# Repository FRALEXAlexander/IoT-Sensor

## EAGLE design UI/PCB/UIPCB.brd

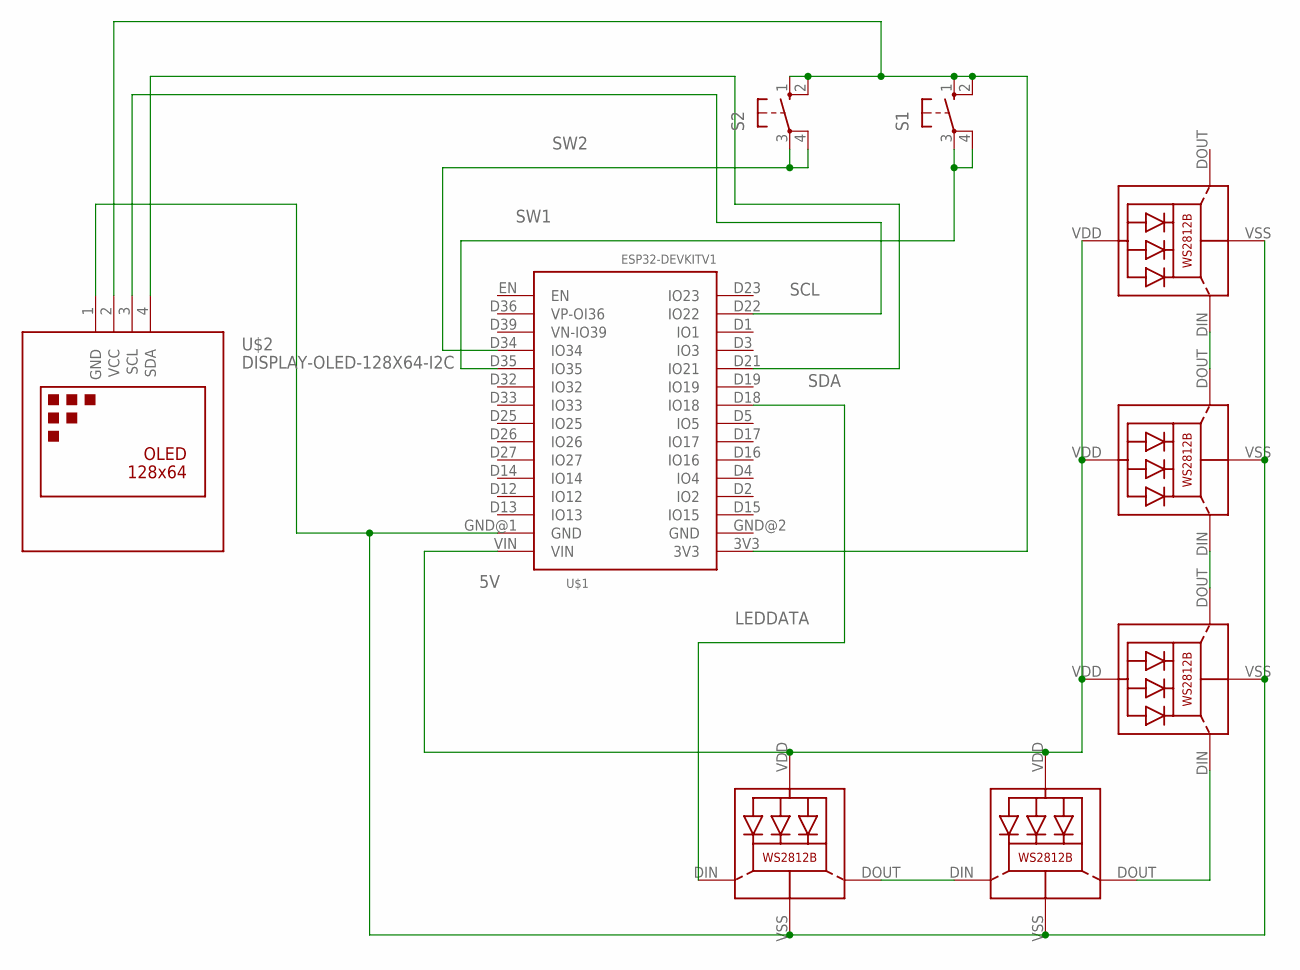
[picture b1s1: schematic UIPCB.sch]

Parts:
LED0, LED1, LED2, LED3, LED4: WS2812B
S1, S2: 10-XX; B3F-10XX
U$1: ESP32DEVKITV1; ESP32-DEVKITV1
U$2: DISPLAY-OLED-128X64-I2C

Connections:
3V3: S1.1 (S), S1.2 (S1), S2.1 (S), S2.2 (S1), U$1.3V3, U$2.2 (VCC)
5V: LED0.VDD, LED1.VDD, LED2.VDD, LED3.VDD, LED4.VDD, U$1.VIN
GND: LED0.VSS (GND), LED1.VSS (GND), LED2.VSS (GND), LED3.VSS (GND), LED4.VSS (GND), U$1.GND@1 (GND), U$2.1 (GND)
LEDDATA: LED0.DIN (DI), U$1.D18 (IO18)
unnamed: LED0.DOUT (DO), LED1.DIN (DI)
unnamed: LED1.DOUT (DO), LED2.DIN (DI)
unnamed: LED2.DOUT (DO), LED3.DIN (DI)
unnamed: LED3.DOUT (DO), LED4.DIN (DI)
SCL: U$1.D22 (IO22), U$2.3 (SCL)
SDA: U$1.D21 (IO21), U$2.4 (SDA)
SW1: S1.3, S1.4 (P1), U$1.D35 (IO35)
SW2: S2.3, S2.4 (P1), U$1.D34 (IO34)

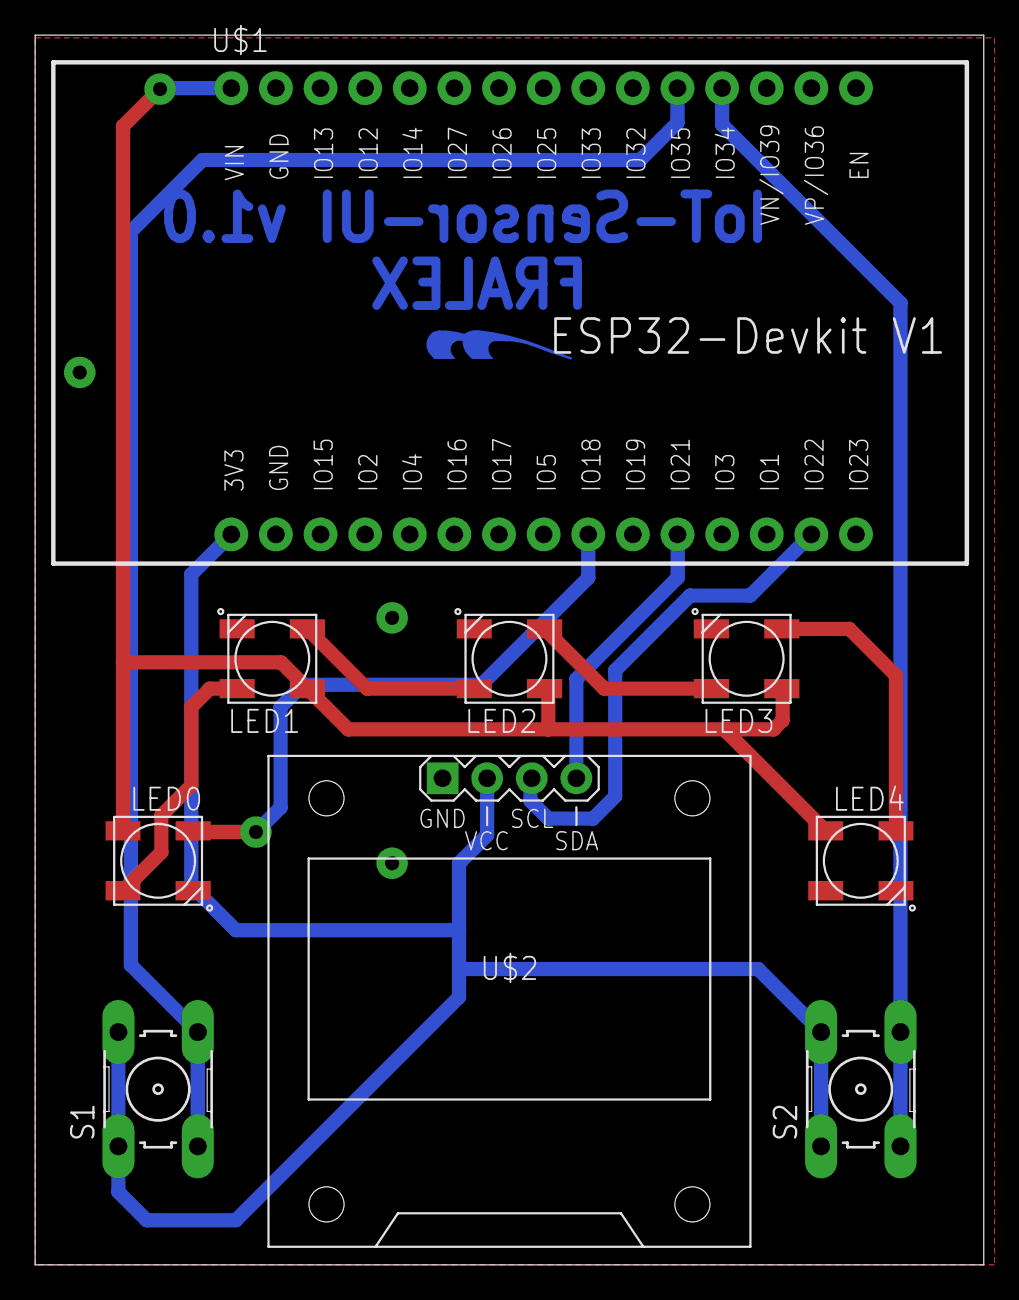
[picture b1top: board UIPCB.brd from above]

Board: 2 copper layers, 54.0 x 70.0 mm, 10 parts (0 on the bottom side), 12 nets.

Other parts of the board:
U$4: LOGOBOTTOM

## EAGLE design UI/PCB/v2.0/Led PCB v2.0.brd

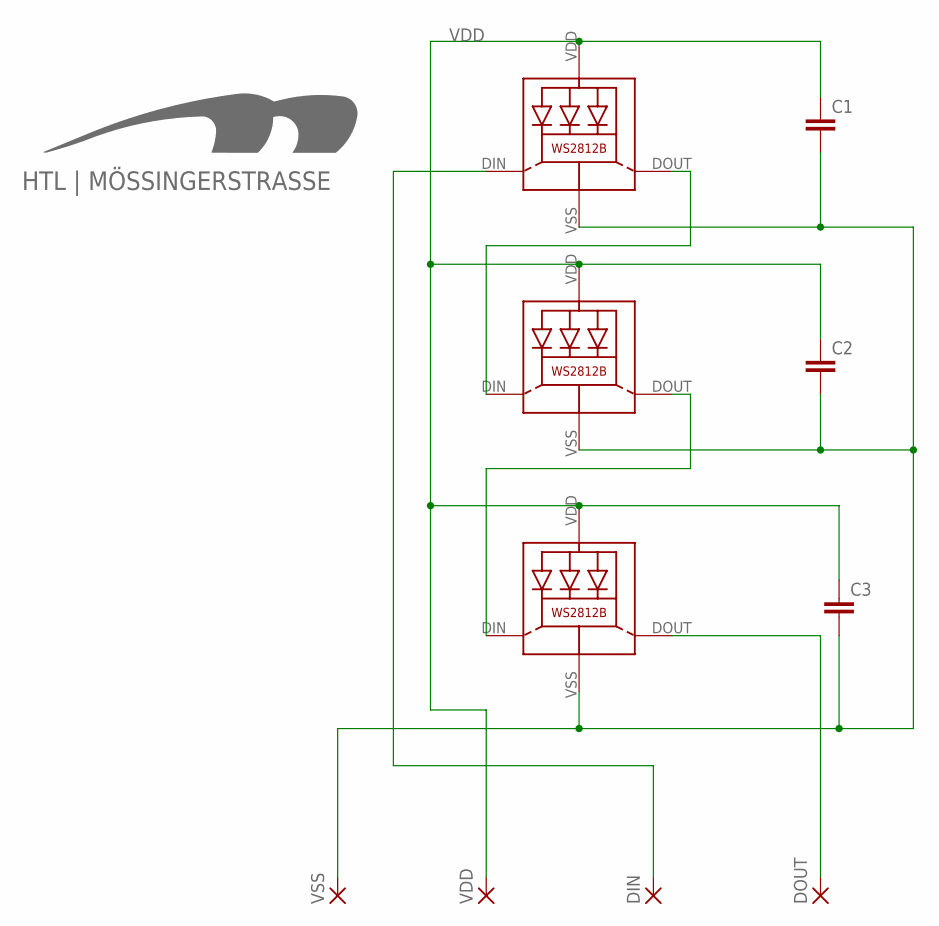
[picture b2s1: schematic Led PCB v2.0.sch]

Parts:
C1, C2, C3: C-EUC0805; C0805
DIN: SMD2; SMD1,27-2,54
DOUT: SMD2; SMD1,27-2,54
LED1, LED2, LED3: WS2812B
U$1: HTL_LOGOTOP_8MM; LOGOTOP_8
VDD: SMD2; SMD1,27-2,54
VSS: SMD2; SMD1,27-2,54

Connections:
DIN: DIN.1, LED1.DIN (DI)
DOUT: DOUT.1, LED3.DOUT (DO)
GND: C1.2, C2.2, C3.2, LED1.VSS (GND), LED2.VSS (GND), LED3.VSS (GND), VSS.1
unnamed: LED2.DOUT (DO), LED3.DIN (DI)
unnamed: LED1.DOUT (DO), LED2.DIN (DI)
VDD: C1.1, C2.1, C3.1, LED1.VDD, LED2.VDD, LED3.VDD, VDD.1

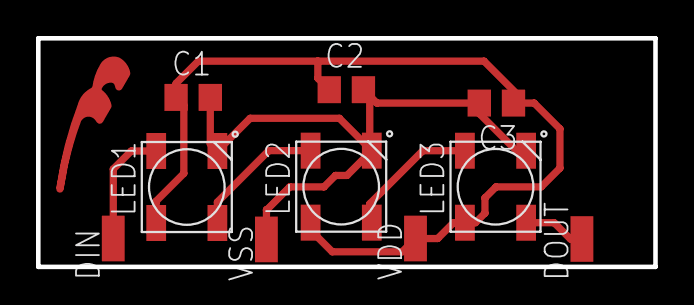
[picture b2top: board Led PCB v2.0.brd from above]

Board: 2 copper layers, 34.3 x 12.7 mm, 11 parts (0 on the bottom side), 6 nets.

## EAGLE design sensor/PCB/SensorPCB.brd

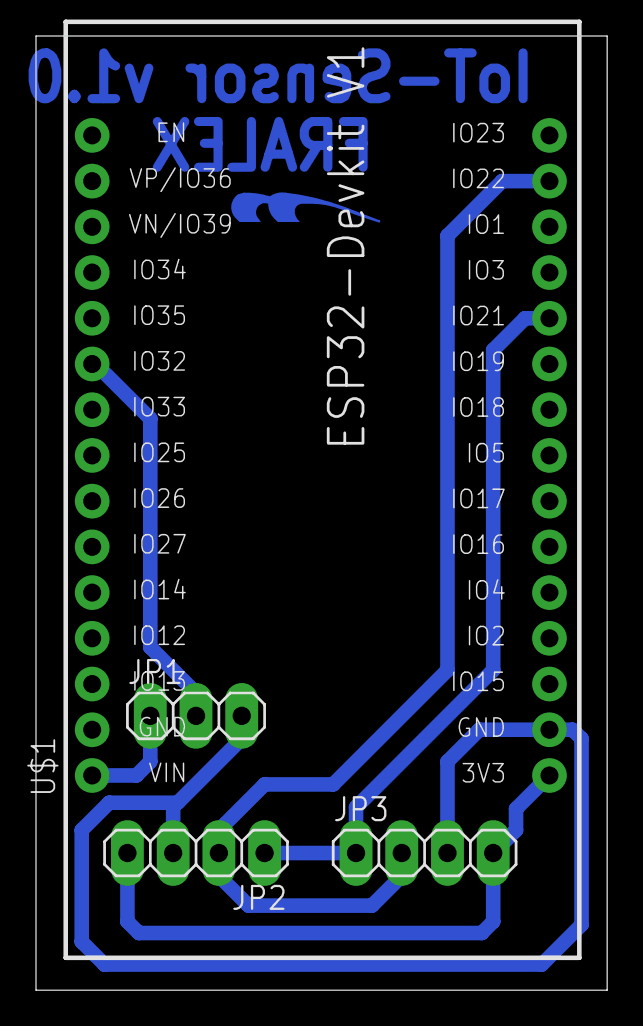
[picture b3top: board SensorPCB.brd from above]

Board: 2 copper layers, 31.7 x 53.0 mm, 5 parts (0 on the bottom side), 6 nets.

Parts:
JP1: 1X03
JP2, JP3: 1X04
U$1: ESP32DEVKITV1; ESP32-DEVKITV1
U$4: LOGOBOTTOM

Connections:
3V3: JP2.4, JP3.4, U$1.3V3
5V: JP1.1, U$1.VIN
GND: JP1.3, JP2.3, JP3.3, U$1.GND@2
MD: JP1.2, U$1.D32
SCL: JP2.2, JP3.2, U$1.D22
SDA: JP2.1, JP3.1, U$1.D21

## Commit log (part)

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2020-02-21 added Sensor PCB and Motionsensor TestScript
2020-02-25 added Script
2020-02-25 moved PCB folder added Case
2020-02-28 added case v2
2020-02-28 added UI Base
2020-02-28 added code for bme / added LED TMP PCB
2020-02-28 Circuit for UI
2020-02-28 Auto stash before merge of "master" and "origin/master"
2020-02-29 added bottom Case changed corner angle
2020-02-29 sorted code added OTA
2020-03-06 added ui board added dashborad basic
2020-03-06 Script Leds
2020-03-13 made it work
2020-04-05 Bump acorn from 6.4.0 to 6.4.1 in /sensor/DASHBOARD
    Bumps [acorn](https://github.com/acornjs/acorn) from 6.4.0 to 6.4.1.
    - [Release notes](https://github.com/acornjs/acorn/releases)
    - [Commits](https://github.com/acornjs/acorn/compare/6.4.0...6.4.1)
2020-06-07 Bump websocket-extensions from 0.1.3 to 0.1.4 in /sensor/DASHBOARD
    Bumps [websocket-extensions](https://github.com/faye/websocket-extensions-node) from 0.1.3 to 0.1.4.
    - [Release notes](https://github.com/faye/websocket-extensions-node/releases)
    - [Changelog](https://github.com/faye/websocket-extensions-node/blob/master/CHANGELOG.md)
    - [Commits](https://github.com/faye/websocket-extensions-node/compare/0.1.3...0.1.4)
2020-07-19 Bump lodash from 4.17.15 to 4.17.19 in /sensor/DASHBOARD
    Bumps [lodash](https://github.com/lodash/lodash) from 4.17.15 to 4.17.19.
    - [Release notes](https://github.com/lodash/lodash/releases)
    - [Commits](https://github.com/lodash/lodash/compare/4.17.15...4.17.19)
2020-08-01 Bump elliptic from 6.5.2 to 6.5.3 in /sensor/DASHBOARD
    Bumps [elliptic](https://github.com/indutny/elliptic) from 6.5.2 to 6.5.3.
    - [Release notes](https://github.com/indutny/elliptic/releases)
    - [Commits](https://github.com/indutny/elliptic/compare/v6.5.2...v6.5.3)
2020-09-11 Bump http-proxy from 1.18.0 to 1.18.1 in /sensor/DASHBOARD
    Bumps [http-proxy](https://github.com/http-party/node-http-proxy) from 1.18.0 to 1.18.1.
    - [Release notes](https://github.com/http-party/node-http-proxy/releases)
    - [Changelog](https://github.com/http-party/node-http-proxy/blob/master/CHANGELOG.md)
    - [Commits](https://github.com/http-party/node-http-proxy/compare/1.18.0...1.18.1)
2020-11-25 Bump highlight.js from 9.18.1 to 9.18.5 in /sensor/DASHBOARD
    Bumps [highlight.js](https://github.com/highlightjs/highlight.js) from 9.18.1 to 9.18.5.
    - [Release notes](https://github.com/highlightjs/highlight.js/releases)
    - [Changelog](https://github.com/highlightjs/highlight.js/blob/9.18.5/CHANGES.md)
    - [Commits](https://github.com/highlightjs/highlight.js/compare/9.18.1...9.18.5)
2021-03-31 Bump y18n from 4.0.0 to 4.0.1 in /sensor/DASHBOARD
    Bumps [y18n](https://github.com/yargs/y18n) from 4.0.0 to 4.0.1.
    - [Release notes](https://github.com/yargs/y18n/releases)
    - [Changelog](https://github.com/yargs/y18n/blob/master/CHANGELOG.md)
    - [Commits](https://github.com/yargs/y18n/commits)
2021-04-30 Bump ssri from 6.0.1 to 6.0.2 in /sensor/DASHBOARD
    Bumps [ssri](https://github.com/npm/ssri) from 6.0.1 to 6.0.2.
    - [Release notes](https://github.com/npm/ssri/releases)
    - [Changelog](https://github.com/npm/ssri/blob/v6.0.2/CHANGELOG.md)
    - [Commits](https://github.com/npm/ssri/compare/v6.0.1...v6.0.2)
2021-05-09 Bump url-parse from 1.4.7 to 1.5.1 in /sensor/DASHBOARD
    Bumps [url-parse](https://github.com/unshiftio/url-parse) from 1.4.7 to 1.5.1.
    - [Release notes](https://github.com/unshiftio/url-parse/releases)
    - [Commits](https://github.com/unshiftio/url-parse/compare/1.4.7...1.5.1)
2021-05-11 Bump lodash from 4.17.15 to 4.17.21 in /sensor/DASHBOARD
    Bumps [lodash](https://github.com/lodash/lodash) from 4.17.15 to 4.17.21.
    - [Release notes](https://github.com/lodash/lodash/releases)
    - [Commits](https://github.com/lodash/lodash/compare/4.17.15...4.17.21)
2021-05-11 Bump hosted-git-info from 2.8.8 to 2.8.9 in /sensor/DASHBOARD
    Bumps [hosted-git-info](https://github.com/npm/hosted-git-info) from 2.8.8 to 2.8.9.
    - [Release notes](https://github.com/npm/hosted-git-info/releases)
    - [Changelog](https://github.com/npm/hosted-git-info/blob/v2.8.9/CHANGELOG.md)
    - [Commits](https://github.com/npm/hosted-git-info/compare/v2.8.8...v2.8.9)
2021-05-26 Bump browserslist from 4.9.1 to 4.16.6 in /sensor/DASHBOARD
    Bumps [browserslist](https://github.com/browserslist/browserslist) from 4.9.1 to 4.16.6.
    - [Release notes](https://github.com/browserslist/browserslist/releases)
    - [Changelog](https://github.com/browserslist/browserslist/blob/main/CHANGELOG.md)
    - [Commits](https://github.com/browserslist/browserslist/compare/4.9.1...4.16.6)
2021-05-28 Bump dns-packet from 1.3.1 to 1.3.4 in /sensor/DASHBOARD
    Bumps [dns-packet](https://github.com/mafintosh/dns-packet) from 1.3.1 to 1.3.4.
    - [Release notes](https://github.com/mafintosh/dns-packet/releases)
    - [Changelog](https://github.com/mafintosh/dns-packet/blob/master/CHANGELOG.md)
    - [Commits](https://github.com/mafintosh/dns-packet/compare/v1.3.1...v1.3.4)
2021-06-16 Bump postcss from 7.0.27 to 7.0.36 in /sensor/DASHBOARD
    Bumps [postcss](https://github.com/postcss/postcss) from 7.0.27 to 7.0.36.
    - [Release notes](https://github.com/postcss/postcss/releases)
    - [Changelog](https://github.com/postcss/postcss/blob/main/CHANGELOG.md)
    - [Commits](https://github.com/postcss/postcss/compare/7.0.27...7.0.36)
    ---
    updated-dependencies:
2021-08-12 Bump path-parse from 1.0.6 to 1.0.7 in /sensor/DASHBOARD
    Bumps [path-parse](https://github.com/jbgutierrez/path-parse) from 1.0.6 to 1.0.7.
    - [Release notes](https://github.com/jbgutierrez/path-parse/releases)
    - [Commits](https://github.com/jbgutierrez/path-parse/commits/v1.0.7)
    ---
    updated-dependencies:
    - dependency-name: path-parse
2021-10-06 Bump url-parse from 1.4.7 to 1.5.3 in /sensor/DASHBOARD
    Bumps [url-parse](https://github.com/unshiftio/url-parse) from 1.4.7 to 1.5.3.
    - [Release notes](https://github.com/unshiftio/url-parse/releases)
    - [Commits](https://github.com/unshiftio/url-parse/compare/1.4.7...1.5.3)
    ---
    updated-dependencies:
    - dependency-name: url-parse
2022-01-14 Bump follow-redirects from 1.10.0 to 1.14.7 in /sensor/DASHBOARD
    Bumps [follow-redirects](https://github.com/follow-redirects/follow-redirects) from 1.10.0 to 1.14.7.
    - [Release notes](https://github.com/follow-redirects/follow-redirects/releases)
    - [Commits](https://github.com/follow-redirects/follow-redirects/compare/v1.10.0...v1.14.7)
    ---
    updated-dependencies:
    - dependency-name: follow-redirects
2022-02-13 Bump ajv from 6.12.0 to 6.12.6 in /sensor/DASHBOARD
    Bumps [ajv](https://github.com/ajv-validator/ajv) from 6.12.0 to 6.12.6.
    - [Release notes](https://github.com/ajv-validator/ajv/releases)
    - [Commits](https://github.com/ajv-validator/ajv/compare/v6.12.0...v6.12.6)
    ---
    updated-dependencies:
    - dependency-name: ajv
2022-02-13 Bump follow-redirects from 1.10.0 to 1.14.8 in /sensor/DASHBOARD
    Bumps [follow-redirects](https://github.com/follow-redirects/follow-redirects) from 1.10.0 to 1.14.8.
    - [Release notes](https://github.com/follow-redirects/follow-redirects/releases)
    - [Commits](https://github.com/follow-redirects/follow-redirects/compare/v1.10.0...v1.14.8)
    ---
    updated-dependencies:
    - dependency-name: follow-redirects
2022-02-27 Bump url-parse from 1.4.7 to 1.5.10 in /sensor/DASHBOARD
    Bumps [url-parse](https://github.com/unshiftio/url-parse) from 1.4.7 to 1.5.10.
    - [Release notes](https://github.com/unshiftio/url-parse/releases)
    - [Commits](https://github.com/unshiftio/url-parse/compare/1.4.7...1.5.10)
    ---
    updated-dependencies:
    - dependency-name: url-parse
2022-04-29 Bump async from 2.6.3 to 2.6.4 in /sensor/DASHBOARD
    Bumps [async](https://github.com/caolan/async) from 2.6.3 to 2.6.4.
    - [Release notes](https://github.com/caolan/async/releases)
    - [Changelog](https://github.com/caolan/async/blob/v2.6.4/CHANGELOG.md)
    - [Commits](https://github.com/caolan/async/compare/v2.6.3...v2.6.4)
    ---
    updated-dependencies:
2022-06-01 Bump eventsource from 1.0.7 to 1.1.1 in /sensor/DASHBOARD
    Bumps [eventsource](https://github.com/EventSource/eventsource) from 1.0.7 to 1.1.1.
    - [Release notes](https://github.com/EventSource/eventsource/releases)
    - [Changelog](https://github.com/EventSource/eventsource/blob/master/HISTORY.md)
    - [Commits](https://github.com/EventSource/eventsource/compare/v1.0.7...v1.1.1)
    ---
    updated-dependencies:
2022-06-23 Bump shell-quote from 1.7.2 to 1.7.3 in /sensor/DASHBOARD
    Bumps [shell-quote](https://github.com/substack/node-shell-quote) from 1.7.2 to 1.7.3.
    - [Release notes](https://github.com/substack/node-shell-quote/releases)
    - [Changelog](https://github.com/substack/node-shell-quote/blob/master/CHANGELOG.md)
    - [Commits](https://github.com/substack/node-shell-quote/compare/v1.7.2...1.7.3)
    ---
    updated-dependencies:
2022-07-18 Bump thenify from 3.3.0 to 3.3.1 in /sensor/DASHBOARD
    Bumps [thenify](https://github.com/thenables/thenify) from 3.3.0 to 3.3.1.
    - [Release notes](https://github.com/thenables/thenify/releases)
    - [Changelog](https://github.com/thenables/thenify/blob/master/History.md)
    - [Commits](https://github.com/thenables/thenify/compare/3.3.0...3.3.1)
    ---
    updated-dependencies:
2022-07-20 Bump terser from 4.6.4 to 4.8.1 in /sensor/DASHBOARD
    Bumps [terser](https://github.com/terser/terser) from 4.6.4 to 4.8.1.
    - [Release notes](https://github.com/terser/terser/releases)
    - [Changelog](https://github.com/terser/terser/blob/master/CHANGELOG.md)
    - [Commits](https://github.com/terser/terser/commits)
    ---
    updated-dependencies:
2022-11-28 Bump node-forge from 0.9.0 to 1.3.1 in /sensor/DASHBOARD
    Bumps [node-forge](https://github.com/digitalbazaar/forge) from 0.9.0 to 1.3.1.
    - [Release notes](https://github.com/digitalbazaar/forge/releases)
    - [Changelog](https://github.com/digitalbazaar/forge/blob/main/CHANGELOG.md)
    - [Commits](https://github.com/digitalbazaar/forge/compare/0.9.0...v1.3.1)
    ---
    updated-dependencies:
2022-11-28 Bump postcss from 7.0.27 to 7.0.39 in /sensor/DASHBOARD
    Bumps [postcss](https://github.com/postcss/postcss) from 7.0.27 to 7.0.39.
    - [Release notes](https://github.com/postcss/postcss/releases)
    - [Changelog](https://github.com/postcss/postcss/blob/7.0.39/CHANGELOG.md)
    - [Commits](https://github.com/postcss/postcss/compare/7.0.27...7.0.39)
    ---
    updated-dependencies:
2022-11-28 Bump ansi-html and webpack-dev-server in /sensor/DASHBOARD
    Removes [ansi-html](https://github.com/Tjatse/ansi-html). It's no longer used after updating ancestor dependency [webpack-dev-server](https://github.com/webpack/webpack-dev-server). These dependencie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
    Removes `ansi-html`
    Updates `webpack-dev-server` from 3.10.3 to 4.11.1
    - [Release notes](https://github.com/webpack/webpack-dev-server/releases)
    - [Changelog](https://github.com/webpack/webpack-dev-server/blob/master/CHANGELOG.md)
    - [Commits](https://github.com/webpack/webpack-dev-server/compare/v3.10.3...v4.11.1)
2022-11-28 Bump is-svg and postcss-svgo in /sensor/DASHBOARD
    Removes [is-svg](https://github.com/sindresorhus/is-svg). It's no longer used after updating ancestor dependency [postcss-svgo](https://github.com/cssnano/cssnano). These dependencies need to be upda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
    Removes `is-svg`
    Updates `postcss-svgo` from 4.0.2 to 5.1.0
    - [Release notes](https://github.com/cssnano/cssnano/releases)
    - [Commits](https://github.com/cssnano/cssnano/compare/4.0.2...postcss-svgo@5.1.0)
    ---
2022-11-29 updated package-lock
2023-01-09 Bump json5 from 1.0.1 to 1.0.2 in /sensor/DASHBOARD
    Bumps [json5](https://github.com/json5/json5) from 1.0.1 to 1.0.2.
    - [Release notes](https://github.com/json5/json5/releases)
    - [Changelog](https://github.com/json5/json5/blob/main/CHANGELOG.md)
    - [Commits](https://github.com/json5/json5/compare/v1.0.1...v1.0.2)
    ---
    updated-dependencies:

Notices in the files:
parts and their libraries:
SSD1306: Released under the Creative Commons Attribution 4.0 International License: http://creativecommons.org/licenses/by/4.0
